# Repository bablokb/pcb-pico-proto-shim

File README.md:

Protoyping Shim for the Raspberry Pi Pico
=========================================

This is a small prototyping shim for the Pico. Besides
the normal 2x20 through holes for the Pico, the PCB also
provides additional holes for the connection of peripherals.
Most importantly there are multiple connectors for GND and 3V3
available.

Schematic
---------

Layout
------

3D-Views
--------

License
-------

[![CC BY-SA 4.0][cc-by-sa-shield]][cc-by-sa]

This work is licensed under a
[Creative Commons Attribution-ShareAlike 4.0 International
License][cc-by-sa].

[![CC BY-SA 4.0][cc-by-sa-image]][cc-by-sa]

[cc-by-sa]: http://creativecommons.org/licenses/by-sa/4.0/
[cc-by-sa-image]: https://licensebuttons.net/l/by-sa/4.0/88x31.png
[cc-by-sa-shield]:
https://img.shields.io/badge/License-CC%20BY--SA%204.0-lightgrey.svg

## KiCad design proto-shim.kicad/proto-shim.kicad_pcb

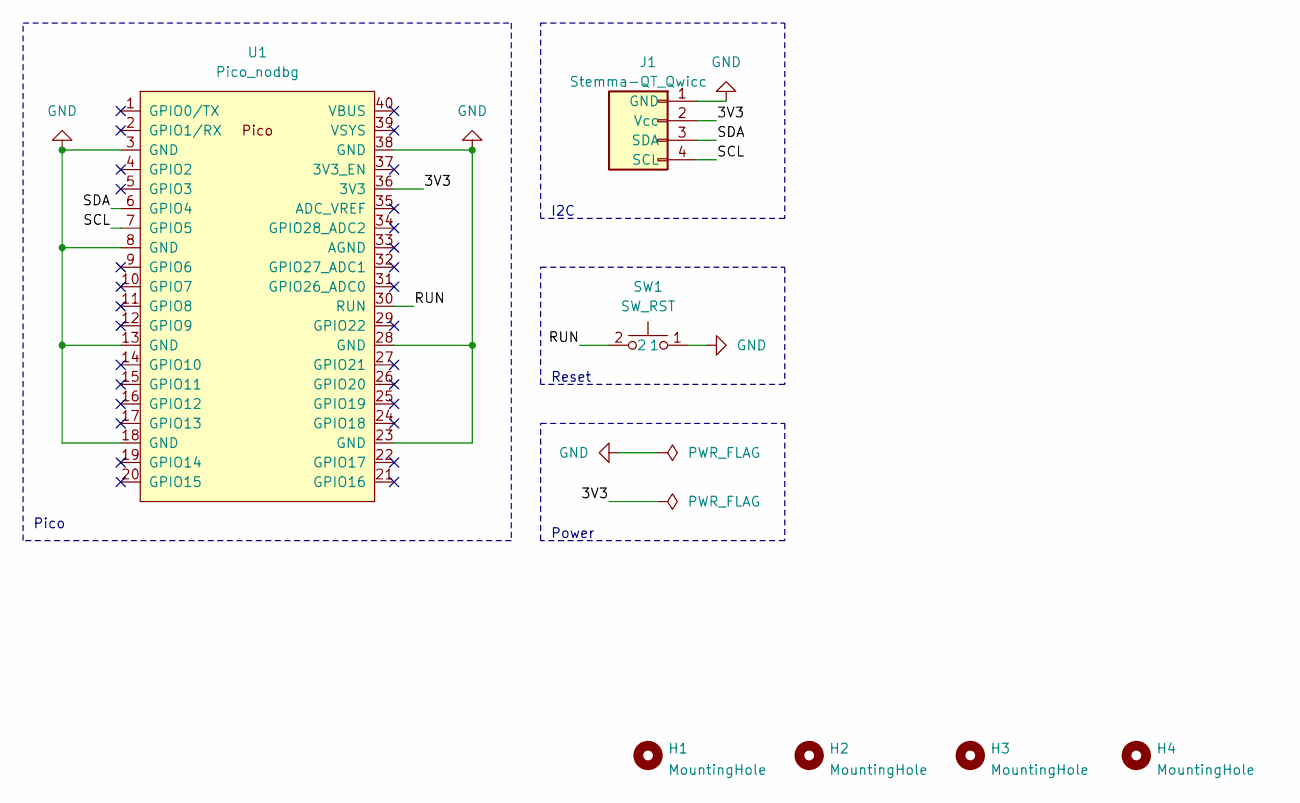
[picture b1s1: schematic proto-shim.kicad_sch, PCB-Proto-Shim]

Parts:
H1, H2, H3, H4: MountingHole; MountingHole_2.5mm
J1: Stemma-QT_Qwicc; JST_SH_SM04B-SRSS-TB_1x04-1MP_P1.00mm_Horizontal
SW1: SW_RST; SW_PUSH_1x_6mm
U1: Pico_nodbg; RPi_Pico_SMD_TH_extended

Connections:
/3V3: J1.2 (Vcc), U1.36 (3V3)
/RUN: SW1.2, U1.30 (RUN)
/SCL: J1.4 (SCL), U1.7 (GPIO5)
/SDA: J1.3 (SDA), U1.6 (GPIO4)
GND: J1.1 (GND), SW1.1, U1.3 (GND), U1.8 (GND), U1.13 (GND), U1.18 (GND), U1.23 (GND), U1.28 (GND), U1.38 (GND)

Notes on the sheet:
Reset
Pico
Power
I2C

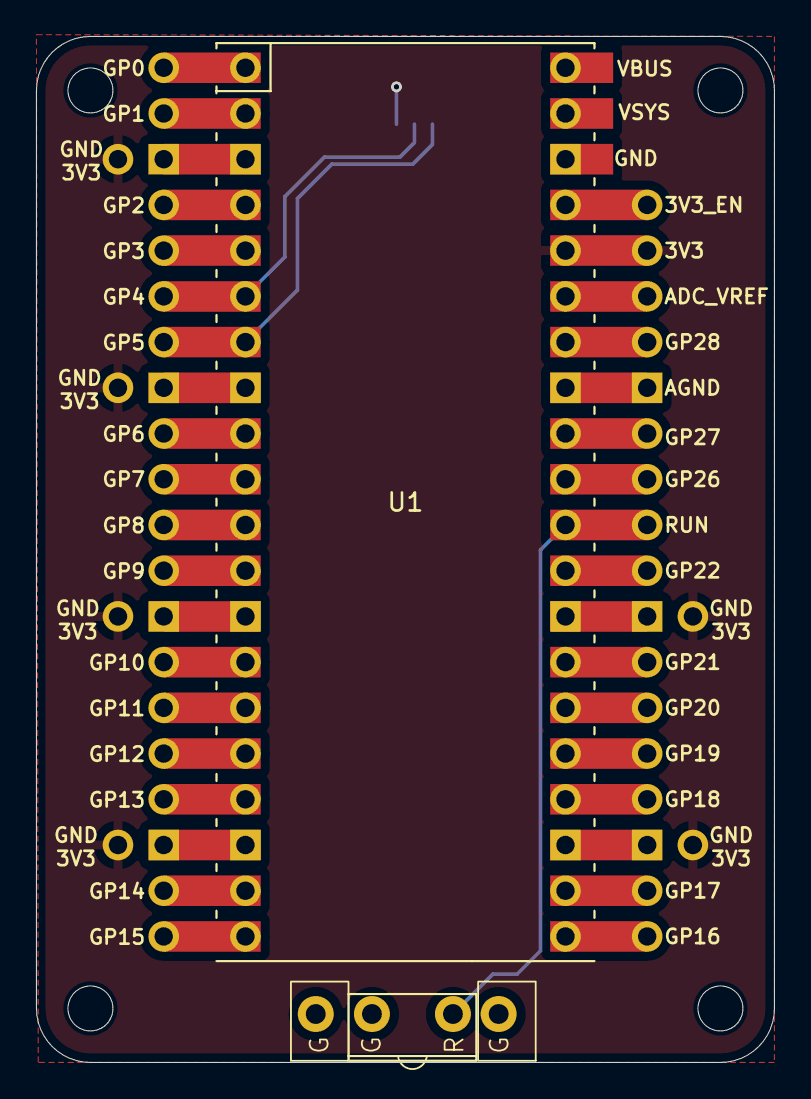
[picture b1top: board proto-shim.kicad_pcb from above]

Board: 2 copper layers, 41.0 x 57.0 mm, 7 parts (1 on the bottom side), 5 nets.

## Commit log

2025-02-01 added description
2025-02-01 fix: remove second link to layout
